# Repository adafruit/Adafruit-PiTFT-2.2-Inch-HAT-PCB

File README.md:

## Adafruit PiTFT 2.2 Inch LCD Display HAT
<a href="http://www.adafruit.com/products/2315"><br/>
Click here to purchase one from the Adafruit shop</a>

The cute PiTFT got even more adorable with this little primary display for Raspberry Pi in HAT form! It features a 2.2" display with 320x240 16-bit color pixels. The HAT uses the high speed SPI interface on the Pi and can use the mini display as a console, X window port, displaying images or video etc. Best of all it plugs right in on top of your Model A+ or B+ and fits into our case quite nicely.

It's designed to plug directly onto the Raspberry Pi 2, Pi 3, Pi Zero or Raspberry Pi 1 Model A+ or B+ . While not specifically designed for Pi Model A or B, you can use it with A/B if you solder in an extra-tall 2x13 header (not included) instead of the included 2x20 header

This design uses the hardware SPI pins (SCK, MOSI, MISO, CE0, CE1) as well as GPIO #25. All other GPIO are unused and are available on a 25-pin long breakout line. Since we had a tiny bit of space, there's 4 flat tactile switches wired to four GPIOs, that you can use if you want to make a basic user interface. For example, you can use one as a power on/off button.

Comes as a fully assembled display PCB and an additional 2x20 GPIO header. Some light soldering is required to attach the 2x20 GPIO header to the HAT but it's fast and easy for anyone with a soldering iron and solder.

PCB files for Adafruit PiTFT 2.2" HAT. The format is EagleCAD schematic and board layout
- https://www.adafruit.com/product/2315

### License

Adafruit invests time and resources providing this open source design, please support Adafruit and open-source hardware by purchasing products from [Adafruit](https://www.adafruit.com)!

All text above must be included in any redistribution

Designed by Limor Fried/Ladyada for Adafruit Industries.
Creative Commons Attribution/Share-Alike, all text above must be included in any redistribution. 
See license.txt for additional information.

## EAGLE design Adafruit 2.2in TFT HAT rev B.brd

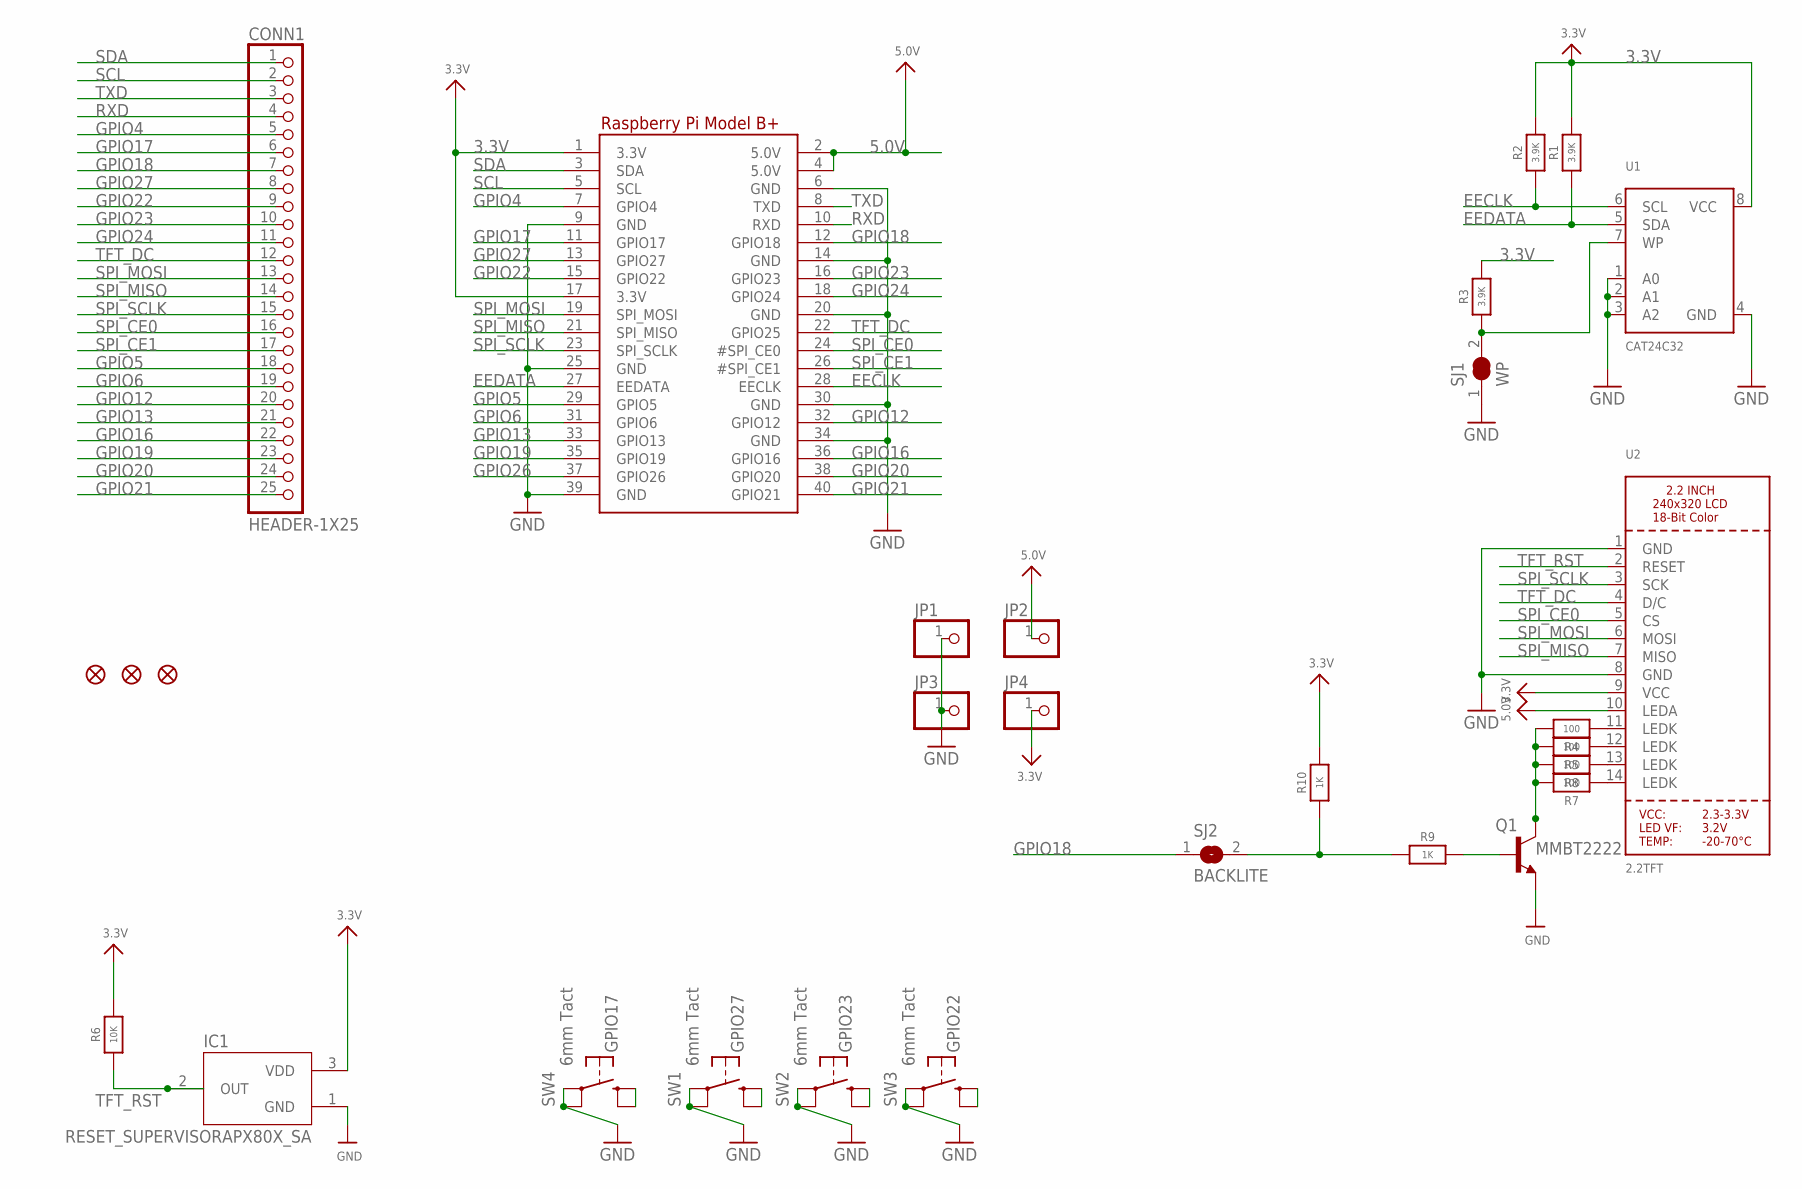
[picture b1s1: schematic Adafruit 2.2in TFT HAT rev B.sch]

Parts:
CONN1: HEADER-1X25; 1X25_ROUND_70MIL
FID1, FID2, FID3: FIDUCIAL_1MM
IC1: RESET_SUPERVISORAPX80X_SA; SOT23-WIDE
JP1, JP2, JP3, JP4: HEADER-1X1ROUND; 1X01_ROUND
Q1: MMBT2222; SOT23-BEC
R1, R2, R3: 3.9K; 0805-NO
R4, R5, R7, R8: 100; 0805-NO
R6: 10K; 0805-NO
R9, R10: 1K; 0805-NO
RPI1: RASPBERRYPI_BPLUS_HATNODIM; PI_HAT_NODIM
SJ1: WP; SOLDERJUMPER_CLOSEDWIRE
SJ2: BACKLITE; SOLDERJUMPER_CLOSEDWIRE
SW1, SW2, SW3, SW4: 6mm Tact; EVQ-Q2
U1: CAT24C32; SOIC8_150MIL
U2: 2.2TFT; TM022HDH26_2.2IN_LCD

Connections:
3.3V: IC1.3 (VDD), JP4.1, R1.2, R2.2, R3.2, R6.2, R10.2, RPI1.1 (3.3V), RPI1.17 (3.3V), U1.8 (VCC), U2.9 (VCC)
5.0V: JP2.1, RPI1.2 (5.0V), RPI1.4 (5.0V), U2.10 (LEDA)
EECLK: R2.1, RPI1.28 (EECLK), U1.6 (SCL)
EEDATA: R1.1, RPI1.27 (EEDATA), U1.5 (SDA)
GND: IC1.1 (GND), JP1.1, JP3.1, Q1.E, RPI1.6 (GND), RPI1.9 (GND), RPI1.14 (GND), RPI1.20 (GND), RPI1.25 (GND), RPI1.30 (GND), RPI1.34 (GND), RPI1.39 (GND), SJ1.1, SW1.A, SW1.A' (P1), SW2.A, SW2.A' (P1), SW3.A, SW3.A' (P1), SW4.A, SW4.A' (P1), U1.1 (A0), U1.2 (A1), U1.3 (A2), U1.4 (GND), U2.1 (GND), U2.8 (GND)
GPIO4: CONN1.5, RPI1.7 (GPIO4)
GPIO5: CONN1.18, RPI1.29 (GPIO5)
GPIO6: CONN1.19, RPI1.31 (GPIO6)
GPIO12: CONN1.20, RPI1.32 (GPIO12)
GPIO13: CONN1.21, RPI1.33 (GPIO13)
GPIO16: CONN1.22, RPI1.36 (GPIO16)
GPIO17: CONN1.6, RPI1.11 (GPIO17), SW4.B (S), SW4.B' (S1)
GPIO18: CONN1.7, RPI1.12 (GPIO18), SJ2.1
GPIO19: CONN1.23, RPI1.35 (GPIO19)
GPIO20: CONN1.24, RPI1.38 (GPIO20)
GPIO21: CONN1.25, RPI1.40 (GPIO21)
GPIO22: CONN1.9, RPI1.15 (GPIO22), SW3.B (S), SW3.B' (S1)
GPIO23: CONN1.10, RPI1.16 (GPIO23), SW2.B (S), SW2.B' (S1)
GPIO24: CONN1.11, RPI1.18 (GPIO24)
GPIO26: RPI1.37 (GPIO26)
GPIO27: CONN1.8, RPI1.13 (GPIO27), SW1.B (S), SW1.B' (S1)
unnamed: R4.1, U2.11 (LEDK)
unnamed: R5.1, U2.12 (LEDK)
unnamed: R7.1, U2.14 (LEDK)
unnamed: R8.1, U2.13 (LEDK)
unnamed: Q1.C, R4.2, R5.2, R7.2, R8.2
unnamed: Q1.B, R9.2
unnamed: R9.1, R10.1, SJ2.2
unnamed: R3.1, SJ1.2, U1.7 (WP)
RXD: CONN1.4, RPI1.10 (RXD)
SCL: CONN1.2, RPI1.5 (SCL)
SDA: CONN1.1, RPI1.3 (SDA)
SPI_CE0: CONN1.16, RPI1.24 (#SPI_CE0), U2.5 (CS)
SPI_CE1: CONN1.17, RPI1.26 (#SPI_CE1)
SPI_MISO: CONN1.14, RPI1.21 (SPI_MISO), U2.7 (MISO)
SPI_MOSI: CONN1.13, RPI1.19 (SPI_MOSI), U2.6 (MOSI)
SPI_SCLK: CONN1.15, RPI1.23 (SPI_SCLK), U2.3 (SCK)
TFT_DC: CONN1.12, RPI1.22 (GPIO25), U2.4 (D/C)
TFT_RST: IC1.2 (OUT), R6.1, U2.2 (RESET)
TXD: CONN1.3, RPI1.8 (TXD)

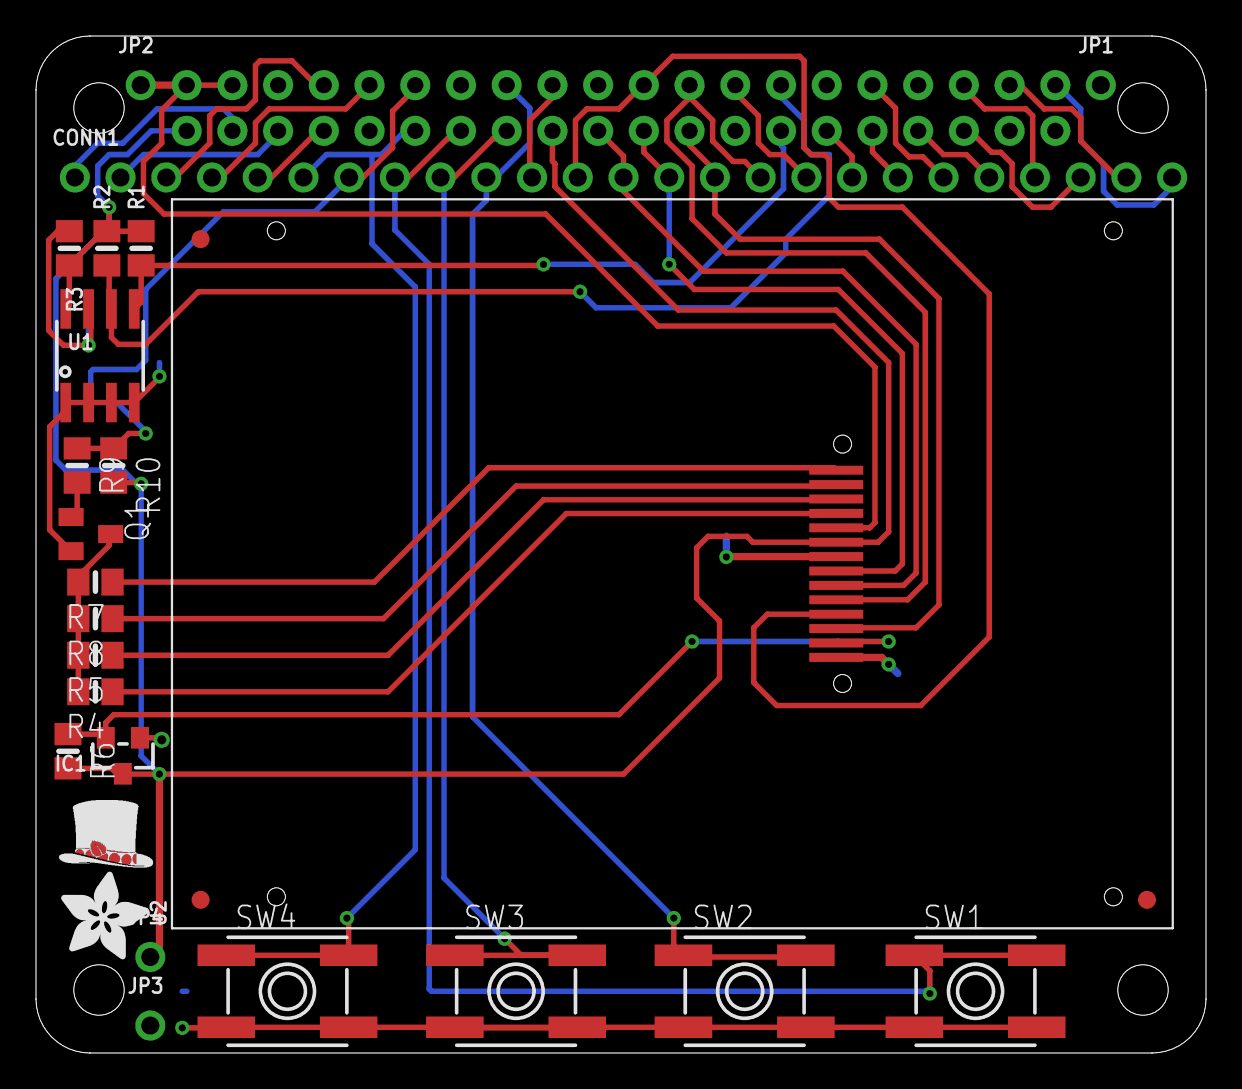
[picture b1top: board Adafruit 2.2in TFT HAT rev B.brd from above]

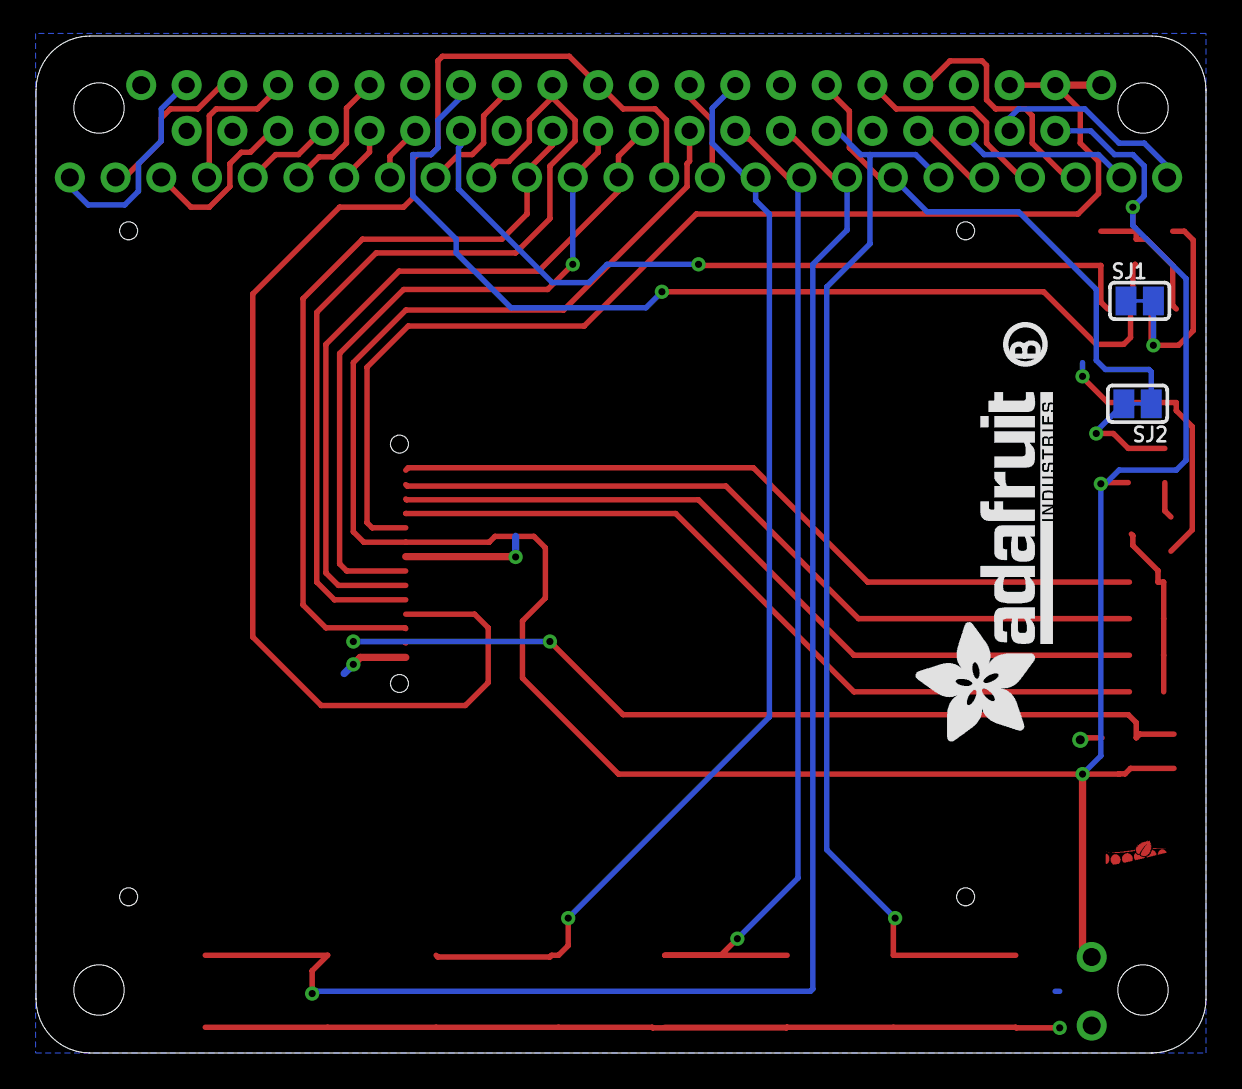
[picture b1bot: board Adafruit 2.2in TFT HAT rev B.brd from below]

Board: 2 copper layers, 65.0 x 56.5 mm, 69 parts (6 on the bottom side), 39 nets.

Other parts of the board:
PLABEL0: PLABEL0
PLABEL1: PLABEL1
PLABEL2: PLABEL2
PLABEL3: PLABEL3
PLABEL4: PLABEL4
PLABEL5: PLABEL5
PLABEL6: PLABEL6
PLABEL7: PLABEL7
PLABEL8: PLABEL8
PLABEL9: PLABEL9
PLABEL10: PLABEL10
PLABEL11: PLABEL11
PLABEL12: PLABEL12
PLABEL13: PLABEL13
PLABEL14: PLABEL14
PLABEL15: PLABEL15
PLABEL16: PLABEL16
PLABEL17: PLABEL17
PLABEL18: PLABEL18
PLABEL19: PLABEL19
PLABEL20: PLABEL20
PLABEL21: PLABEL21
PLABEL22: PLABEL22
PLABEL23: PLABEL23
PLABEL24: PLABEL24
PLABEL25: PLABEL25
PLABEL26: PLABEL26
PLABEL27: PLABEL27
PLABEL28: PLABEL28
PLABEL29: PLABEL29
PLABEL30: PLABEL30
PLABEL31: PLABEL31
PLABEL32: PLABEL32
PLABEL33: PLABEL33
PLABEL34: PLABEL34
PLABEL35: PLABEL35
U$1: ADAFRUIT_5MM
U$3: ADAFRUIT_TEXT_20MM
U$4: PIHATLOGO
U$12: PCBFEAT-REV-056

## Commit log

2015-12-08 init!
2025-11-18 add rev b

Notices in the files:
parts and their libraries:
microbuilder: This work is placed in the public domain, and may be freely used for commercial and non-commercial work with the following conditions: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
